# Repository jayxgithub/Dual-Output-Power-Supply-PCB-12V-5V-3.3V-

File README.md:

# ⚡ Dual Output Power Supply PCB (12V → 5V & 3.3V)

## 📌 Project Overview

This project is a **custom-designed PCB power supply module** created using **KiCad**, which efficiently converts a **12V DC input** into **regulated 5V and 3.3V outputs**.

It is designed for use in **embedded systems, IoT devices, and microcontroller-based projects** where stable dual voltage rails are required.

---

## 🎯 Key Features

* 🔋 Converts **12V DC → 5V & 3.3V**
* ⚙️ Uses **linear voltage regulators (LD1117 series)**
* 🛡️ Includes **input protection using fuses**
* 💡 LED indicators for power status
* 🔌 Multiple terminal connectors for easy interfacing
* 🧩 4 Layer PCB Design

---

## 🛠️ Tools & Technologies

* **KiCad** (Schematic + PCB Design)
* **PCB Layout Design**
* **Electronic Components (Through-hole + SMD)**
* **Basic Power Electronics Concepts**

---

## ⚙️ Working Principle

1. **Input Stage**

   * 12V DC is supplied through connectors.
   * Fuses provide protection against overcurrent.

2. **Voltage Regulation**

   * **LD1117S50** → Regulates 12V to **5V**
   * **LD1117S33** → Regulates 12V to **3.3V**

3. **Filtering**

   * Capacitors remove noise and stabilize voltage.

4. **Indication**

   * LEDs indicate power presence on outputs.

---

## 📂 Repository Structure

```
📁 Dual-Power-Supply-PCB
│── 📄 power supply.kicad_pro      # Project file
│── 📄 power supply.kicad_sch      # Schematic
│── 📄 power supply.kicad_pcb      # PCB layout
│── 📄 BOM.csv                     # Components list
│── 📁 images/                     # PCB screenshots (top/bottom/3D)
│── 📄 README.md                   # Project documentation
```

---

## 📋 Bill of Materials (BOM)

| Id | Designator     | Footprint                             | Qty | Value/Designation  |
| -- | -------------- | ------------------------------------- | --- | ------------------ |
| 1  | F4, F1, F2, F3 | Fuseholder_TR5_Littelfuse_No560_No460 | 4   | Fuse_Small         |
| 2  | R1, R2, R3, R4 | R_1206_3216Metric                     | 4   | 1k                 |
| 3  | C1, C2         | C_1206_3216Metric                     | 2   | 10µF               |
| 4  | C3, C4         | C_1206_3216Metric                     | 2   | 100nF              |
| 5  | C5, C6         | C_1206_3216Metric                     | 2   | 10nF               |
| 6  | C7, C8         | C_1206_3216Metric                     | 2   | 0.1µF              |
| 7  | D1, D2         | LED_D5.0mm                            | 2   | LED Indicator      |
| 8  | J1, J2, J3, J4 | Altech_AK300_1x02_P5.00mm_45-Degree   | 4   | Terminal Block     |
| 9  | SW1, SW2       | SW_DIP_SPSTx01_Piano                  | 2   | Switch             |
| 10 | U1             | SOT-223-3_TabPin2                     | 1   | LD1117S50TR (5V)   |
| 11 | U2             | SOT-223-3_TabPin2                     | 1   | LD1117S33TR (3.3V) |
| 12 | Q1, Q2         | TO-92_Inline                          | 2   | 2N3904             |

---

## 🔍 Design Highlights

* Proper **decoupling capacitor placement** near regulators
* **Wide traces for power lines** to handle current safely
* Clean and organized **component placement**
* Easy-to-understand schematic for learning purposes

---

## 🚀 Applications

* Microcontroller projects (Arduino, ESP32, STM32)
* IoT systems
* Embedded hardware prototypes
* Educational electronics labs

---

## 📸 Preview (Add Screenshots)

> Add images here after uploading:

* PCB Top View
* PCB Bottom View
* 3D View

---

## 📚 Learning Outcomes

* PCB design using KiCad
* Voltage regulation concepts
* Component selection and placement
* Real-world hardware debugging understanding

---

## 👨‍🎓 About Me

I am a **final-year Electronics & Telecommunication Engineering student** passionate about:

* PCB Design
* Embedded Systems
* Python & Automation

This project reflects my hands-on experience in **hardware design and practical electronics**.

---

## ⭐ Future Improvements

* Add **switching regulator (buck converter)** for higher efficiency
* Include **thermal analysis**
* Add **current limiting and protection circuits**
* Compact multilayer PCB design

---

## 🙌 If you like this project

Give it a ⭐ on GitHub and feel free to fork or improve it!

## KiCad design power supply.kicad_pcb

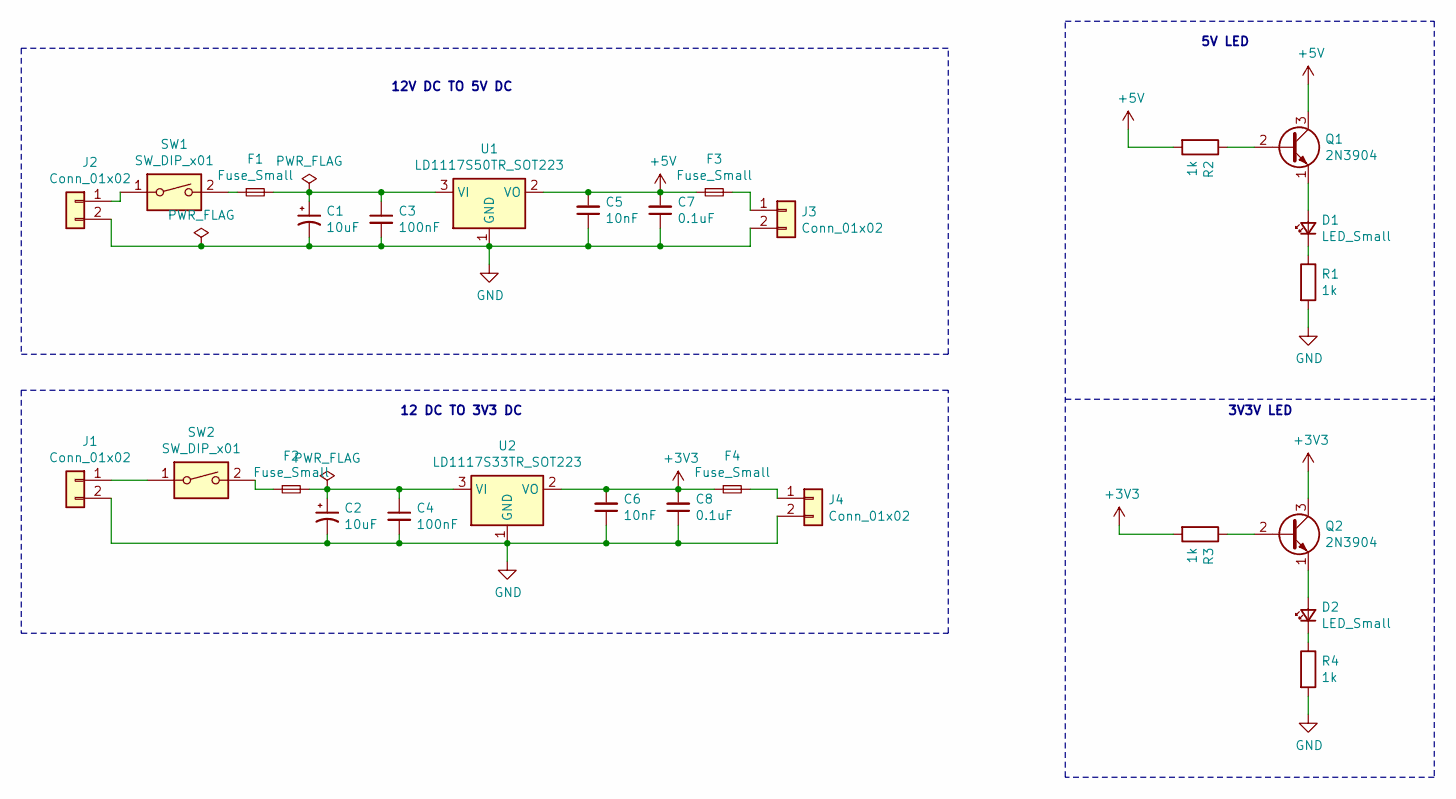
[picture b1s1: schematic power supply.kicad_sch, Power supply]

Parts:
C1, C2: 10uF; C_1206_3216Metric
C3, C4: 100nF; C_1206_3216Metric
C5, C6: 10nF; C_1206_3216Metric
C7, C8: 0.1uF; C_1206_3216Metric
D1, D2: LED_Small; LED_D5.0mm
F1, F2, F3, F4: Fuse_Small; Fuseholder_TR5_Littelfuse_No560_No460
J1, J2, J3, J4: Conn_01x02; Altech_AK300_1x02_P5.00mm_45-Degree
Q1, Q2: 2N3904; TO-92_Inline
R1, R2, R3, R4: 1k; R_1206_3216Metric
SW1, SW2: SW_DIP_x01; SW_DIP_SPSTx01_Piano_10.8x4.1mm_W7.62mm_P2.54mm
U1: LD1117S50TR_SOT223; SOT-223-3_TabPin2
U2: LD1117S33TR_SOT223; SOT-223-3_TabPin2

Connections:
+3V3: C6.2, C8.2, F4.1, Q2.3 (C), R3.2, U2.2 (VO)
+5V: C5.2, C7.2, F3.1, Q1.3 (C), R2.2, U1.2 (VO)
GND: C1.2, C2.2, C3.2, C4.2, C5.1, C6.1, C7.1, C8.1, J1.2, J2.2, J3.2, J4.2, R1.2, R4.2, U1.1 (GND), U2.1 (GND)
unnamed: D1.2 (A), Q1.1 (E)
unnamed: D1.1 (K), R1.1
unnamed: D2.2 (A), Q2.1 (E)
unnamed: D2.1 (K), R4.1
unnamed: F1.1, SW1.2
unnamed: F2.1, SW2.2
unnamed: J1.1, SW2.1
unnamed: J2.1, SW1.1
unnamed: F3.2, J3.1
unnamed: F4.2, J4.1
unnamed: Q1.2 (B), R2.1
unnamed: Q2.2 (B), R3.1
unnamed: C1.1, C3.1, F1.2, U1.3 (VI)
unnamed: C2.1, C4.1, F2.2, U2.3 (VI)

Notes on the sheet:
12 DC TO 3V3 DC
3V3V LED
5V LED
12V DC TO 5V DC

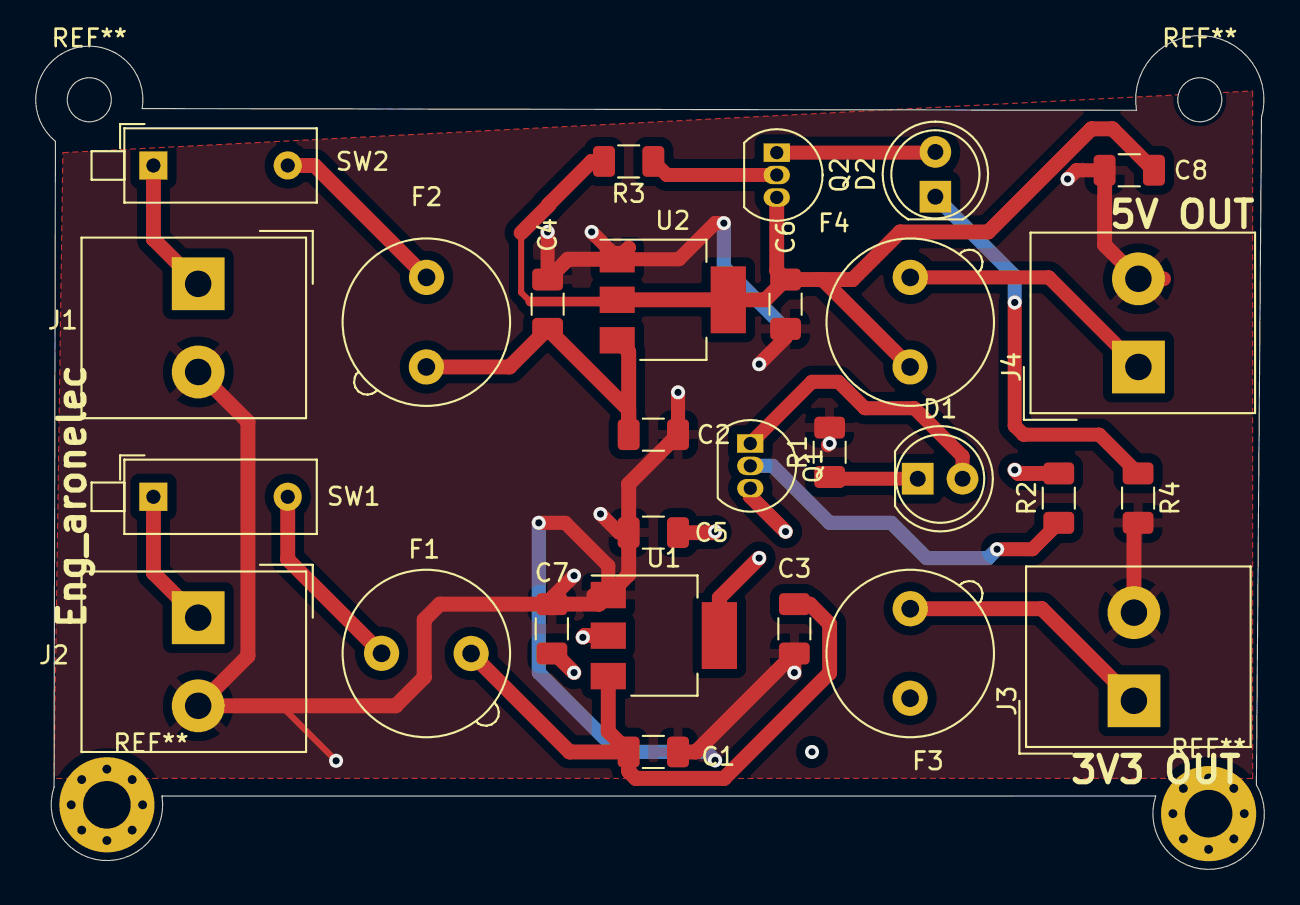
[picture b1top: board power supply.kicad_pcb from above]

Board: 4 copper layers, 69.7 x 47.3 mm, 28 parts (0 on the bottom side), 17 nets.

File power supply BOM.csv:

"Id";"Designator";"Footprint";"Quantity";"Designation";"Supplier and ref";
1;"F4,F1,F2,F3";"Fuseholder_TR5_Littelfuse_No560_No460";4;"Fuse_Small";;;
2;"R1,R2,R3,R4";"R_1206_3216Metric";4;"1k";;;
3;"C1,C2";"C_1206_3216Metric";2;"10uF";;;
4;"C3,C4";"C_1206_3216Metric";2;"100nF";;;
5;"C5,C6";"C_1206_3216Metric";2;"10nF";;;
6;"C7,C8";"C_1206_3216Metric";2;"0.1uF";;;
7;"D1,D2";"LED_D5.0mm";2;"LED_Small";;;
8;"J1,J2,J3,J4";"Altech_AK300_1x02_P5.00mm_45-Degree";4;"Conn_01x02";;;
9;"SW1,SW2";"SW_DIP_SPSTx01_Piano_10.8x4.1mm_W7.62mm_P2.54mm";2;"SW_DIP_x01";;;
10;"U1";"SOT-223-3_TabPin2";1;"LD1117S50TR_SOT223";;;
11;"U2";"SOT-223-3_TabPin2";1;"LD1117S33TR_SOT223";;;
12;"Q1,Q2";"TO-92_Inline";2;"2N3904";;;

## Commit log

2026-05-03 Revise README for Dual Output Power Supply PCB
    Updated the README to enhance project details and structure.
2026-05-03 Update PCB layout description in README
